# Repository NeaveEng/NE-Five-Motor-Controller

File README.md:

NE-Five Motor Driver
==

This is the PCB that controls the wheels and linear actuator on NE-Five, it's a work in progress and used entirely at your own risk. 

Highlights
==

It uses a Pi Pico at its core with four IFX9201SG motor controllers, it has one servo header that includes an analogue feedback pin to control a linear actuator.

Thanks!
==
Many thanks to Mark Mellors, Phillip Skippy McGaw, and Robert Karpinski for incredibly useful feedback!

# automatic image generation
### Images

Using [this github action](https://github.com/linalinn/kicad-render)

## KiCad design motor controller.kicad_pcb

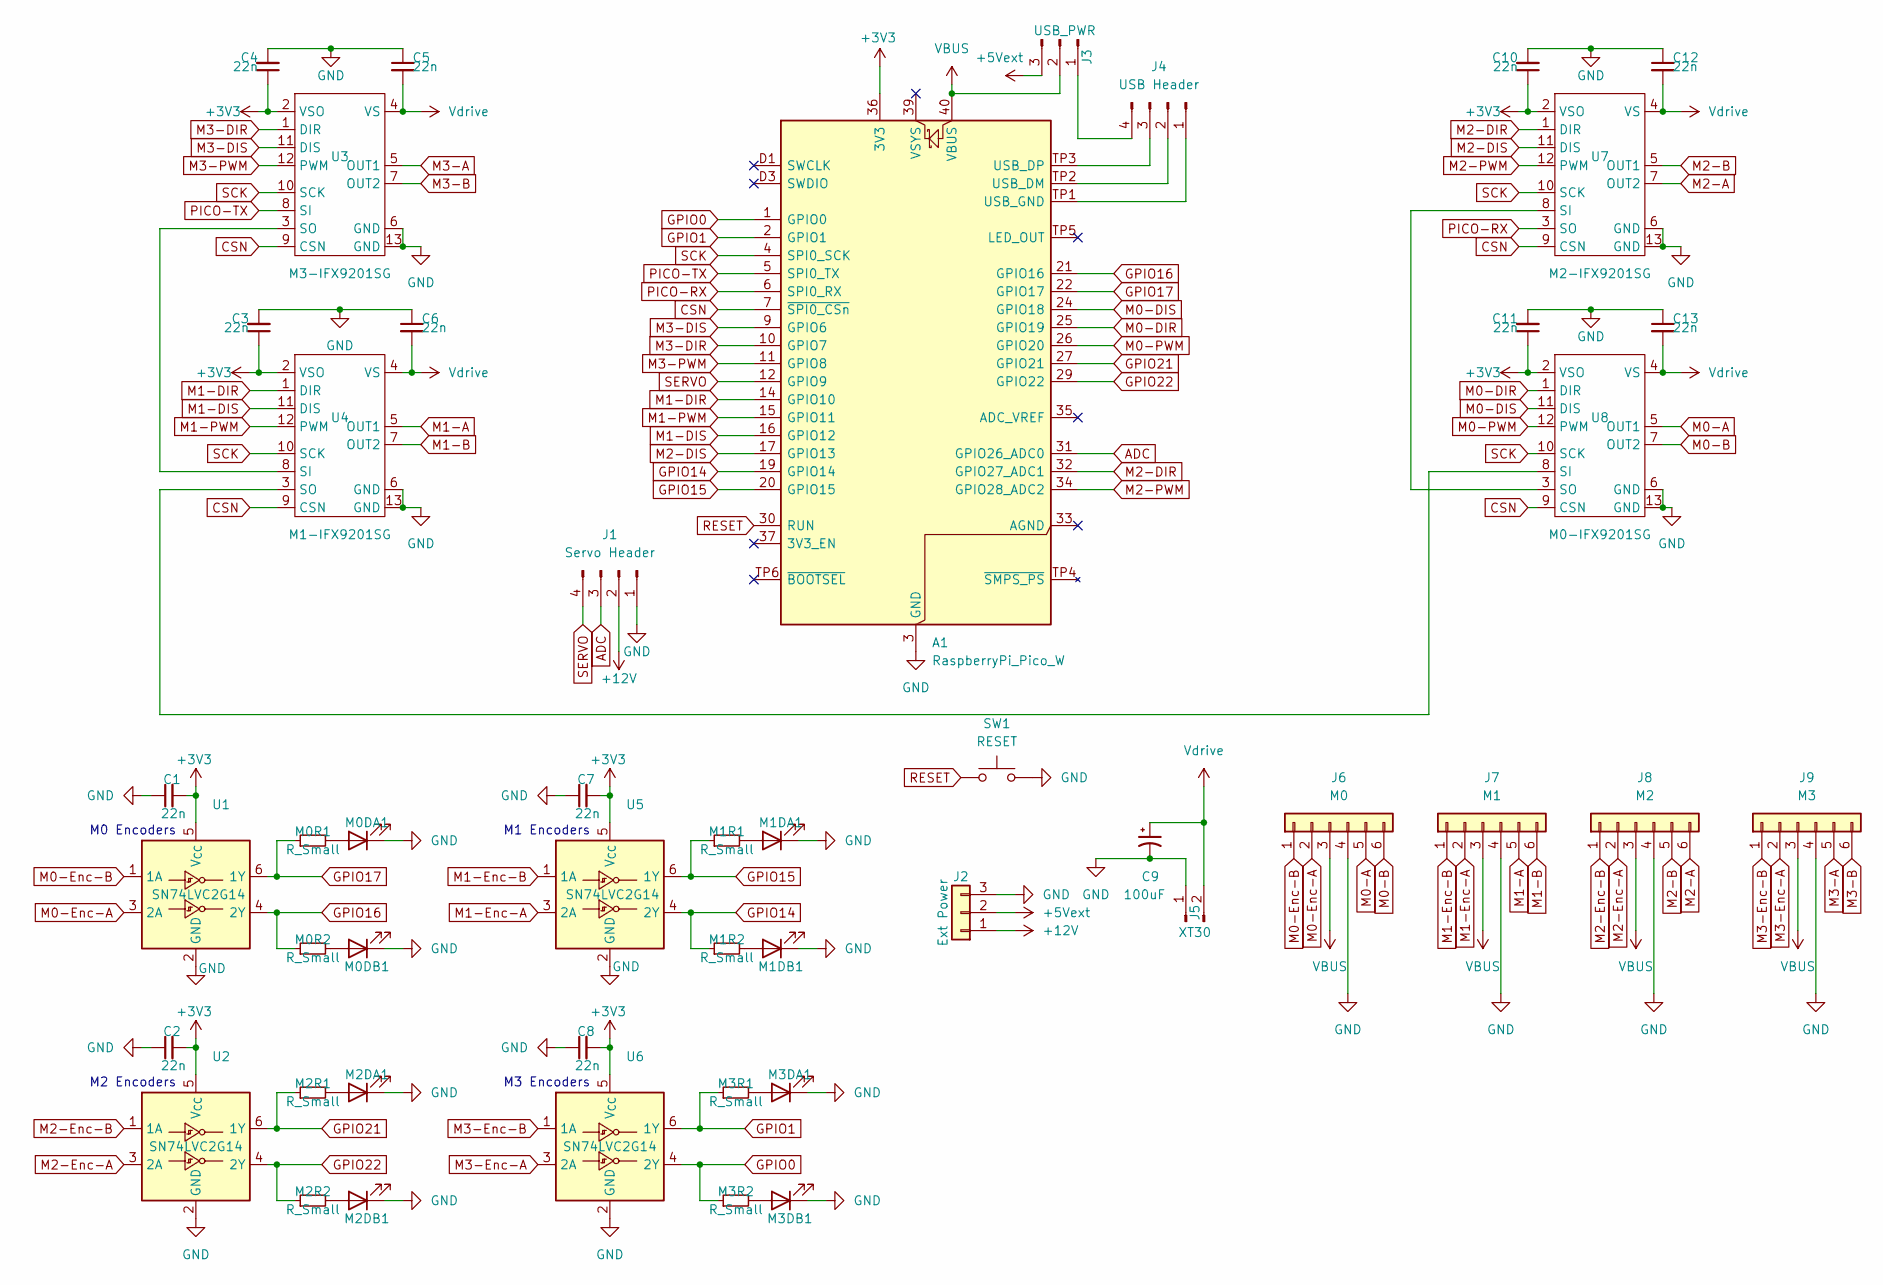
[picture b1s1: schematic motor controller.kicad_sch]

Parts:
A1: RaspberryPi_Pico_W; RaspberryPi_Pico_W_SMD
C1, C2, C3, C4, C5, C6, C7, C8, C10, C11, C12, C13: 22n; C_1206_3216Metric
C9: 100uF; CP_Radial_D6.3mm_P2.50mm
J1: Servo Header; JST_XH_B4B-XH-A_1x04_P2.50mm_Vertical
J2: Ext Power; JST_XH_B3B-XH-A_1x03_P2.50mm_Vertical
J3: USB_PWR; PinHeader_1x03_P2.54mm_Vertical
J4: USB Header; JST_XH_B4B-XH-A_1x04_P2.50mm_Vertical
J5: XT30; AMASS_XT30PW-M_1x02_P2.50mm_Horizontal
J6: M0; JST_XH_B6B-XH-A_1x06_P2.50mm_Vertical
J7: M1; JST_XH_B6B-XH-A_1x06_P2.50mm_Vertical
J8: M2; JST_XH_B6B-XH-A_1x06_P2.50mm_Vertical
J9: M3; JST_XH_B6B-XH-A_1x06_P2.50mm_Vertical
M0DA1, M0DB1, M1DA1, M1DB1, M2DA1, M2DB1, M3DA1, M3DB1: LED; LED_0805_2012Metric
M0R1, M0R2, M1R1, M1R2, M2R1, M2R2, M3R1, M3R2: R_Small; R_0805_2012Metric
SW1: RESET; SW_Push_1P1T_NO_CK_KMR2
U1, U2, U5, U6: SN74LVC2G14; SOT-23-6
U3: M3-IFX9201SG; PG_DSO_12_17
U4: M1-IFX9201SG; PG_DSO_12_17
U7: M2-IFX9201SG; PG_DSO_12_17
U8: M0-IFX9201SG; PG_DSO_12_17

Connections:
+3V3: A1.36 (3V3), C1.2, C2.2, C3.1, C4.1, C7.2, C8.2, C10.1, C11.1, U1.5 (V_{CC}), U2.5 (V_{CC}), U3.2 (VSO), U4.2 (VSO), U5.5 (V_{CC}), U6.5 (V_{CC}), U7.2 (VSO), U8.2 (VSO)
+5Vext: J2.2 (5v), J3.3
+12V: J1.2, J2.1 (GND)
ADC: A1.31 (GPIO26_ADC0), J1.3
CSN: A1.7 (~SPI0_CSn), U3.9 (CSN), U4.9 (CSN), U7.9 (CSN), U8.9 (CSN)
GND: A1.3 (GND), A1.8 (GND), A1.13 (GND), A1.18 (GND), A1.23 (GND), A1.28 (GND), A1.38 (GND), A1.D2 (GND), C1.1, C2.1, C3.2, C4.2, C5.1, C6.1, C7.1, C8.1, C9.2, C10.2, C11.2, C12.1, C13.1, J1.1, J2.3 (12v), J5.1 (-), J6.4, J7.4, J8.4, J9.4, M0DA1.1 (K), M0DB1.1 (K), M1DA1.1 (K), M1DB1.1 (K), M2DA1.1 (K), M2DB1.1 (K), M3DA1.1 (K), M3DB1.1 (K), SW1.2, U1.2 (GND), U2.2 (GND), U3.6 (GND), U3.13 (GND), U4.6 (GND), U4.13 (GND), U5.2 (GND), U6.2 (GND), U7.6 (GND), U7.13 (GND), U8.6 (GND), U8.13 (GND)
GPIO0: A1.1 (GPIO0), M3R2.1, U6.4 (2Y)
GPIO1: A1.2 (GPIO1), M3R1.1, U6.6 (1Y)
GPIO14: A1.19 (GPIO14), M1R2.1, U5.4 (2Y)
GPIO15: A1.20 (GPIO15), M1R1.1, U5.6 (1Y)
GPIO16: A1.21 (GPIO16), M0R2.1, U1.4 (2Y)
GPIO17: A1.22 (GPIO17), M0R1.1, U1.6 (1Y)
GPIO21: A1.27 (GPIO21), M2R1.1, U2.6 (1Y)
GPIO22: A1.29 (GPIO22), M2R2.1, U2.4 (2Y)
M0-A: J6.5, U8.5 (OUT1)
M0-B: J6.6, U8.7 (OUT2)
M0-DIR: A1.25 (GPIO19), U8.1 (DIR)
M0-DIS: A1.24 (GPIO18), U8.11 (DIS)
M0-Enc-A: J6.2, U1.3 (2A)
M0-Enc-B: J6.1, U1.1 (1A)
M0-PWM: A1.26 (GPIO20), U8.12 (PWM)
M1-A: J7.5, U4.5 (OUT1)
M1-B: J7.6, U4.7 (OUT2)
M1-DIR: A1.14 (GPIO10), U4.1 (DIR)
M1-DIS: A1.16 (GPIO12), U4.11 (DIS)
M1-Enc-A: J7.2, U5.3 (2A)
M1-Enc-B: J7.1, U5.1 (1A)
M1-PWM: A1.15 (GPIO11), U4.12 (PWM)
M2-A: J8.6, U7.7 (OUT2)
M2-B: J8.5, U7.5 (OUT1)
M2-DIR: A1.32 (GPIO27_ADC1), U7.1 (DIR)
M2-DIS: A1.17 (GPIO13), U7.11 (DIS)
M2-Enc-A: J8.2, U2.3 (2A)
M2-Enc-B: J8.1, U2.1 (1A)
M2-PWM: A1.34 (GPIO28_ADC2), U7.12 (PWM)
M3-A: J9.5, U3.5 (OUT1)
M3-B: J9.6, U3.7 (OUT2)
M3-DIR: A1.10 (GPIO7), U3.1 (DIR)
M3-DIS: A1.9 (GPIO6), U3.11 (DIS)
M3-Enc-A: J9.2, U6.3 (2A)
M3-Enc-B: J9.1, U6.1 (1A)
M3-PWM: A1.11 (GPIO8), U3.12 (PWM)
unnamed: A1.TP2 (USB_DM), J4.2
unnamed: A1.TP3 (USB_DP), J4.3
unnamed: A1.TP1 (USB_GND), J4.1
unnamed: J3.1, J4.4
unnamed: M0DA1.2 (A), M0R1.2
unnamed: M0DB1.2 (A), M0R2.2
unnamed: M1DA1.2 (A), M1R1.2
unnamed: M1DB1.2 (A), M1R2.2
unnamed: M2DA1.2 (A), M2R1.2
unnamed: M2DB1.2 (A), M2R2.2
unnamed: M3DA1.2 (A), M3R1.2
unnamed: M3DB1.2 (A), M3R2.2
unnamed: U3.3 (SO), U4.8 (SI)
unnamed: U4.3 (SO), U8.8 (SI)
unnamed: U7.8 (SI), U8.3 (SO)
PICO-RX: A1.6 (SPI0_RX), U7.3 (SO)
PICO-TX: A1.5 (SPI0_TX), U3.8 (SI)
RESET: A1.30 (RUN), SW1.1
SCK: A1.4 (SPI0_SCK), U3.10 (SCK), U4.10 (SCK), U7.10 (SCK), U8.10 (SCK)
SERVO: A1.12 (GPIO9), J1.4
VBUS: A1.40 (VBUS), J3.2, J6.3, J7.3, J8.3, J9.3
Vdrive: C5.2, C6.2, C9.1, C12.2, C13.2, J5.2 (+), U3.4 (VS), U4.4 (VS), U7.4 (VS), U8.4 (VS)

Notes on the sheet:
M3 Encoders
M1 Encoders
M2 Encoders
M0 Encoders

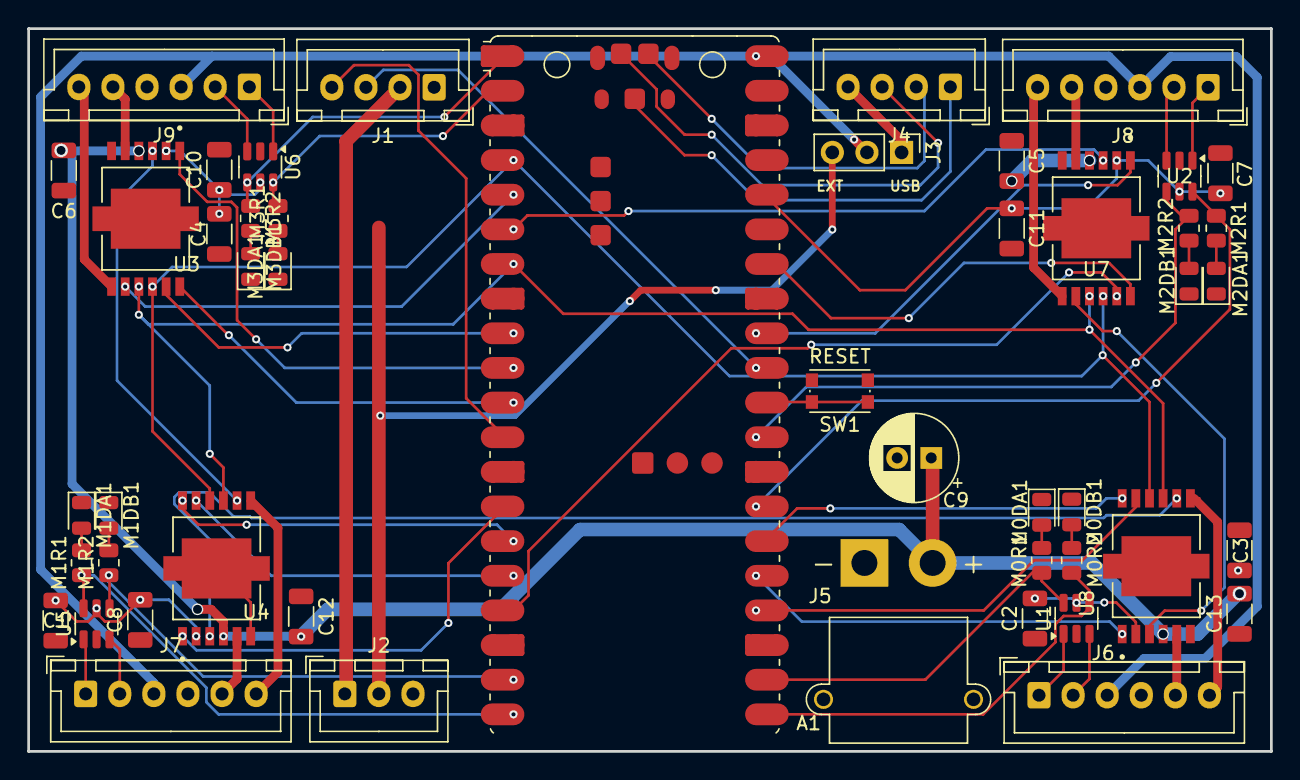
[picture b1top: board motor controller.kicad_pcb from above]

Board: 2 copper layers, 91.1 x 53.0 mm, 48 parts (0 on the bottom side), 64 nets.

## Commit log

2024-11-27 initial checkin
2024-11-27 updated schematic and pcb
2024-11-27 added readme
2024-11-27 changes suggested by Rob
2024-11-27 fixed a short, started updating the PCB layout
2024-11-28 more tweaking
2024-11-28 switched to vertical plugs
2024-11-29 trying again to get the PCB layout to work
2024-11-29 deleted the schematic pdf as it's out of date
2024-12-17 added image generation action
2024-12-17 fixed typo, added ref to tool
